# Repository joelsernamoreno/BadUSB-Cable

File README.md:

# BadUSB-Cable
BadUSB cable project

The developers and collaborators of this project do not earn money with this. 
You can invite me for a coffee to further develop Low-Cost hacking devices. If you don't invite me for a coffee, nothing happens, I will continue developing devices.

**Summary:**
1. Evil Crow Cable
2. Evil Crow Cable Pro
3. Evil Crow Cable Wind
4. Collaborators
	
# Evil Crow Cable

* **Start of the project and first BadUSB cable on breadboard (November 2017)**

* **First BadUSB cable with USB connector (December 2017)**

* **Finished proof of concept (January 2018)**

* **Technical presentation of BadUSB cable and first PCB design (Rev0) presented at Hackplayers Conference (February 2018)**

* **Rev1 of BadUSB cable design (January 2019)**

* **Rev2 of BadUSB cable design (May 2019)**

* **First PCBs (July 2019)**

* **BadUSB Cable Rev2 (August 2019)**

* **Rev3 of BadUSB cable design (September 2019)**

* **Development kit (September 2019)**

* **BadUSB Cable Rev3 (September 2019)**

* **Development kits and complete cables for Navaja Negra Conference (October 2019)**

* **Rev3.1 of BadUSB Cable design (October 2019)**

This version is a solution for Rev3. Rev3 has the holes D- and D+, these holes should NOT be soldered and Rev3 can be confusing.
In Rev3.1 design these holes are eliminated, only VDD and GND are available.
Thanks to @_MG_ for recommending this solution.

* **Evil Crow Cable (November 2019)**

**PROJECT REPOSITORY:** https://github.com/joelsernamoreno/EvilCrow-Cable

# Evil Crow Cable Pro

* **First test PCB with USB Hub for testing microcontrollers (March 2020)**

* **First PoC - Atmega32U4 and Hub USB (June 2020)**

* **First PCB - Atmega32U4 and Hub USB (September 2020)**

* **Second PoC Rev1 - RP2040 (April 2023)**

* **Second PoC Rev2 - RP2040 (April 2023)**

* **Second PoC Rev3 - RP2040 (May 2023)**

* **Second PCB - RP2040 (June 2023)**

* **Second PoC Rev4 - RP2040 and USB Host pads (July 2023)**

* **Final PCB - RP2040 and USB Host pads (August 2023)**

* **Evil Crow Cable Pro (August 2023)**

**PROJECT REPOSITORY:** https://github.com/joelsernamoreno/EvilCrowCable-Pro

# Evil Crow Cable Wind

* **First PoC - Atmega32U4 and ESP8285 (May 2020)**

* **Second PoC - ESP8285 (July 2020)**

* **First PCBs - ESP8285 (August 2020)**

* **Third PoC - ESP32-S2 (September 2022)**

* **First PCB - ESP32-S2 (September 2022)**

* **Final PoC Rev 1 - ESP32-C3 inside a USB Type-C connector (June 2024)**

* **Final PCB Rev 1 - ESP32-C3 inside a USB Type-C connector (July 2024)**

* **Final PoC Rev 2 - ESP32-S3 inside a USB Type-C connector (August 2024)**

* **Final PCB - Evil Crow Cable Wind (August 2024)**

**PROJECT REPOSITORY:** https://github.com/joelsernamoreno/EvilCrowCable-Wind

# Collaborators

**Ignacio Diaz & Forensic Security:**

	* Ignacio Díaz: @Nacon_96

	* Forensic & Security: @ForensicSec

	* https://forensic-security.com

**April Brother:**

	* April Brother: @aprbrother

	* https://www.aprbrother.com

**Ernesto Xload:**

	* Ernesto Xload: @ernesto_xload

**Jorge Mata:**

	* Jorge Mata: @jor_mata

	* Innovart: @innovart_cc

	* https://innovart.cc

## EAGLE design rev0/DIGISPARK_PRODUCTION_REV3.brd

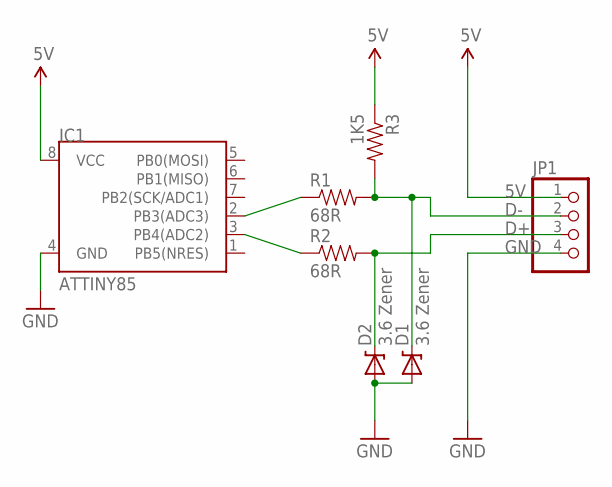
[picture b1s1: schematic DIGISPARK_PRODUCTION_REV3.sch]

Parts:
D1, D2: 3.6 Zener; SOD-323
IC1: ATTINY85; SO08-EIAJ
JP1: PINHD-1X4; 1X04
R1, R2: 68R; 0402-RES
R3: 1K5; 0402-RES

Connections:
5V: IC1.8 (VCC), JP1.1, R3.1
D+: D2.1 (C), JP1.3, R2.2
D-: D1.1 (C), JP1.2, R1.2, R3.2
GND: D1.2 (A), D2.2 (A), IC1.4 (GND), JP1.4
unnamed: IC1.2 (PB3(ADC3)), R1.1
unnamed: IC1.3 (PB4(ADC2)), R2.1

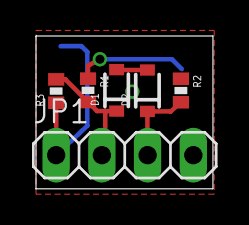
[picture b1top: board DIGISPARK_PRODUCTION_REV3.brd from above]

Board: 2 copper layers, 9.8 x 8.5 mm, 7 parts (1 on the bottom side), 6 nets.

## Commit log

2019-08-08 BadUSB Cable
2019-08-08 README.md
2019-09-18 Installation
2019-10-08 Documentation
2019-10-09 gerbers rev3 and rev3.1
2024-08-02 Add Evil Crow Cable
2024-08-02 Add Evil Crow Cable Pro
2024-08-02 Add Evil Crow Cable Wind

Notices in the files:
parts and their libraries:
SparkFun: Licensing: CC v3.0 Share-Alike You are welcome to use this library for commercial purposes.
SparkFun-Aesthetics: Licensing: Creative Commons ShareAlike 4.0 International - https://creativecommons.org/licenses/by-sa/4.0
